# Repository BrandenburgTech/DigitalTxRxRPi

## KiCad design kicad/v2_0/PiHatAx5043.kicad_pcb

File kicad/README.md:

v1_3 - Digital Transceiver for the Raspberry Pi with the AX5043

v1_3_5 - Digital Transceiver for the Raspberry Pi with the AX5243

v2_0 - Digital Transceiver for the Raspberry Pi with the AX5043, power amplifier, and GPS module

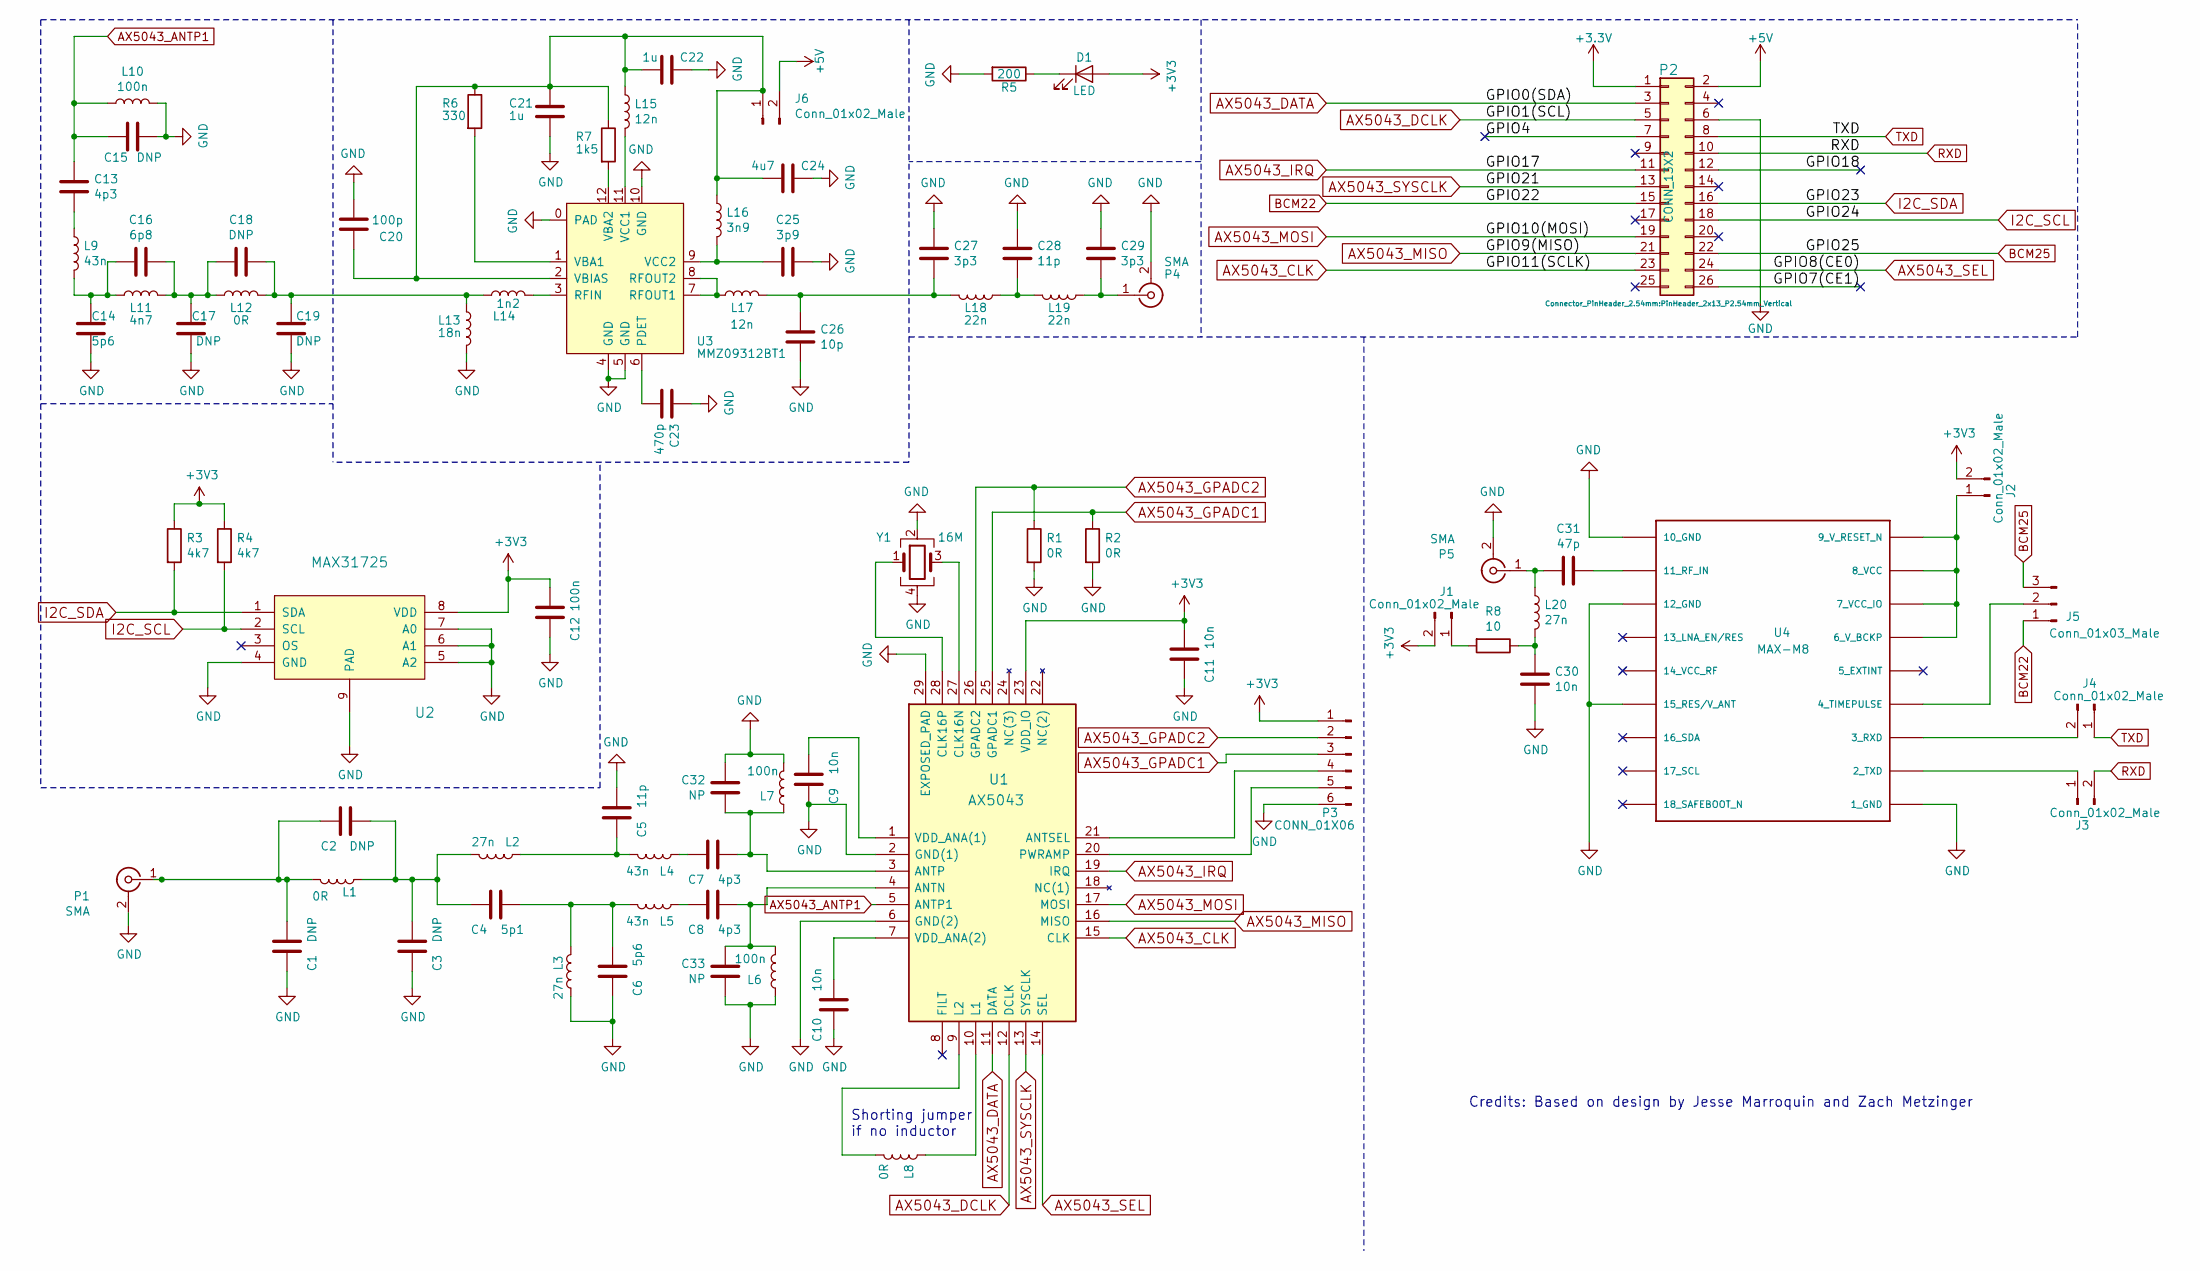
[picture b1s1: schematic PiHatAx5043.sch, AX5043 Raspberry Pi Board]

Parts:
C1, C2, C3, C15, C17, C18, C19: DNP; C_0603_1608Metric
C4: 5p1; C_0603_1608Metric
C5, C28: 11p; C_0603_1608Metric
C6, C14: 5p6; C_0603_1608Metric
C7, C8, C13: 4p3; C_0603_1608Metric
C9, C10, C11, C30: 10n; C_0603_1608Metric
C12: 100n; C_0603_1608Metric
C16: 6p8; C_0603_1608Metric
C20: 100p; C_0603_1608Metric
C21, C22: 1u; C_0603_1608Metric
C23: 470p; C_0603_1608Metric
C24: 4u7; C_0603_1608Metric
C25: 3p9; C_0603_1608Metric
C26: 10p; C_0603_1608Metric
C27, C29: 3p3; C_0603_1608Metric
C31: 47p; C_0603_1608Metric
C32, C33: NP; C_0603_1608Metric
D1: LED; LED_0603_1608Metric
J1, J2, J3, J4, J6: Conn_01x02_Male; PinHeader_1x02_P2.54mm_Vertical
J5: Conn_01x03_Male; PinHeader_1x03_P2.54mm_Vertical
L1, L8, L12: 0R; L_0603_1608Metric
L2, L3, L20: 27n; L_0603_1608Metric
L4, L5, L9: 43n; L_0603_1608Metric
L6, L7, L10: 100n; L_0603_1608Metric
L11: 4n7; L_0603_1608Metric
L13: 18n; L_0603_1608Metric
L14: 1n2; L_0603_1608Metric
L15, L17: 12n; L_0603_1608Metric
L16: 3n9; L_0603_1608Metric
L18, L19: 22n; L_0603_1608Metric
P1, P4, P5: SMA; SMA_Amphenol_901-144_Vertical
P2: CONN_13X2; PinHeader_2x13_P2.54mm_Vertical
P3: CONN_01X06; PinHeader_1x06_P2.54mm_Vertical
R1, R2: 0R; R_0603_1608Metric
R3, R4: 4k7; R_0603_1608Metric
R5: 200; R_0603_1608Metric
R6: 330; R_0603_1608Metric
R7: 1k5; R_0603_1608Metric
R8: 10; R_0603_1608Metric
U1: AX5043; QFN50P500X500X95-29N
U2: MAX31725; DFN-8-1EP_3x3mm_P0.65mm_EP1.55x2.4mm
U3: MMZ09312BT1; QFN-12-1EP_3x3mm_P0.5mm_EP1.65x1.65mm_ThermalVias
U4: MAX-M8
Y1: 16M; Crystal_SMD_ECX42-4pin_4.0x2.5mm

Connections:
+5V: J6.2, P2.2
/GPIO4: P2.7
/GPIO7(CE1): P2.26
/GPIO18: P2.12
AX5043_ANTP1: C13.1, C15.2, L10.1, U1.5 (ANTP1)
AX5043_CLK: P2.23, U1.15 (CLK)
AX5043_DATA: P2.3, U1.11 (DATA)
AX5043_DCLK: P2.5, U1.12 (DCLK)
AX5043_GPADC1: P3.3, R2.1, U1.25 (GPADC1)
AX5043_GPADC2: P3.2, R1.1, U1.26 (GPADC2)
AX5043_IRQ: P2.11, U1.19 (IRQ)
AX5043_MISO: P2.21, U1.16 (MISO)
AX5043_MOSI: P2.19, U1.17 (MOSI)
AX5043_SEL: P2.24, U1.14 (SEL)
AX5043_SYSCLK: P2.13, U1.13 (SYSCLK)
BCM22: J5.1, P2.15
BCM25: J5.3, P2.22
GND: C1.2, C3.2, C5.1, C6.2, C9.2, C10.2, C11.2, C12.2, C14.2, C15.1, C17.2, C19.2, C20.2, C21.2, C22.1, C23.1, C24.1, C25.1, C26.2, C27.1, C28.1, C29.1, C30.2, C32.2, C33.1, L3.1, L6.1, L7.2, L10.2, L13.2, P1.2 (Ext), P2.6, P3.6, P4.2 (Ext), P5.2 (Ext), R1.2, R2.2, R5.2, U1.2 (GND(1)), U1.6 (GND(2)), U1.29 (EXPOSED_PAD), U2.4 (GND), U2.5 (A2), U2.6 (A1), U2.7 (A0), U2.9 (PAD), U3.0 (PAD), U3.4 (GND), U3.5 (GND), U3.10 (GND), U3.13, U4.1_GND, U4.10_GND, U4.12_GND, U4.15_V_ANT/RESERVED (15_RES/V_ANT), Y1.2, Y1.4
I2C_SCL: P2.18, R4.2, U2.2 (SCL)
I2C_SDA: P2.16, R3.2, U2.1 (SDA)
unnamed: C1.1, C2.2, L1.2, P1.1 (In)
unnamed: C2.1, C3.1, C4.2, L1.1, L2.2
unnamed: C4.1, C6.1, L3.2, L5.2
unnamed: C5.2, L2.1, L4.2
unnamed: C7.2, L4.1
unnamed: C8.2, L5.1
unnamed: C9.1, U1.1 (VDD_ANA(1))
unnamed: C10.1, U1.7 (VDD_ANA(2))
unnamed: C13.2, L9.1
unnamed: C14.1, C16.2, L9.2, L11.1
unnamed: C16.1, C17.1, C18.2, L11.2, L12.1
unnamed: C18.1, C19.1, L12.2, L13.1, L14.1
unnamed: C20.1, C21.1, C22.2, C24.2, J6.1, L15.1, L16.1, R6.1, R7.1, U3.2 (VBIAS)
unnamed: C23.2, U3.6 (PDET)
unnamed: C25.2, L16.2, U3.9 (VCC2)
unnamed: C26.1, C27.2, L17.2, L18.2
unnamed: C28.2, L18.1, L19.2
unnamed: C29.2, L19.1, P4.1 (In)
unnamed: C30.1, L20.2, R8.1
unnamed: C31.1, U4.11_RF_IN
unnamed: C31.2, L20.1, P5.1 (In)
unnamed: C7.1, C32.1, L7.1, U1.3 (ANTP)
unnamed: C8.1, C33.2, L6.2, U1.4 (ANTN)
unnamed: D1.1 (K), R5.1
unnamed: J1.1, R8.2
unnamed: J2.1, U4.6_V_BCKP, U4.7_VCC_IO, U4.8_VCC, U4.9_RESET_N (9_V_RESET_N)
unnamed: J3.1, U4.2_TXD
unnamed: J4.2, U4.3_RXD
unnamed: J5.2, U4.4_TIMEPULSE
unnamed: L8.1, U1.10 (L1)
unnamed: L8.2, U1.9 (L2)
unnamed: L14.2, U3.3 (RFIN)
unnamed: L15.2, U3.11 (VCC1)
unnamed: L17.1, U3.7 (RFOUT1), U3.8 (RFOUT2)
unnamed: P3.4, U1.21 (ANTSEL)
unnamed: P3.5, U1.20 (PWRAMP)
unnamed: R6.2, U3.1 (VBA1)
unnamed: R7.2, U3.12 (VBA2)
unnamed: U1.27 (CLK16N), Y1.3
unnamed: U1.28 (CLK16P), Y1.1
RXD: J3.2, P2.10
TXD: J4.1, P2.8

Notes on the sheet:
Shorting jumper if no inductor
Credits: Based on design by Jesse Marroquin and Zach Metzinger

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
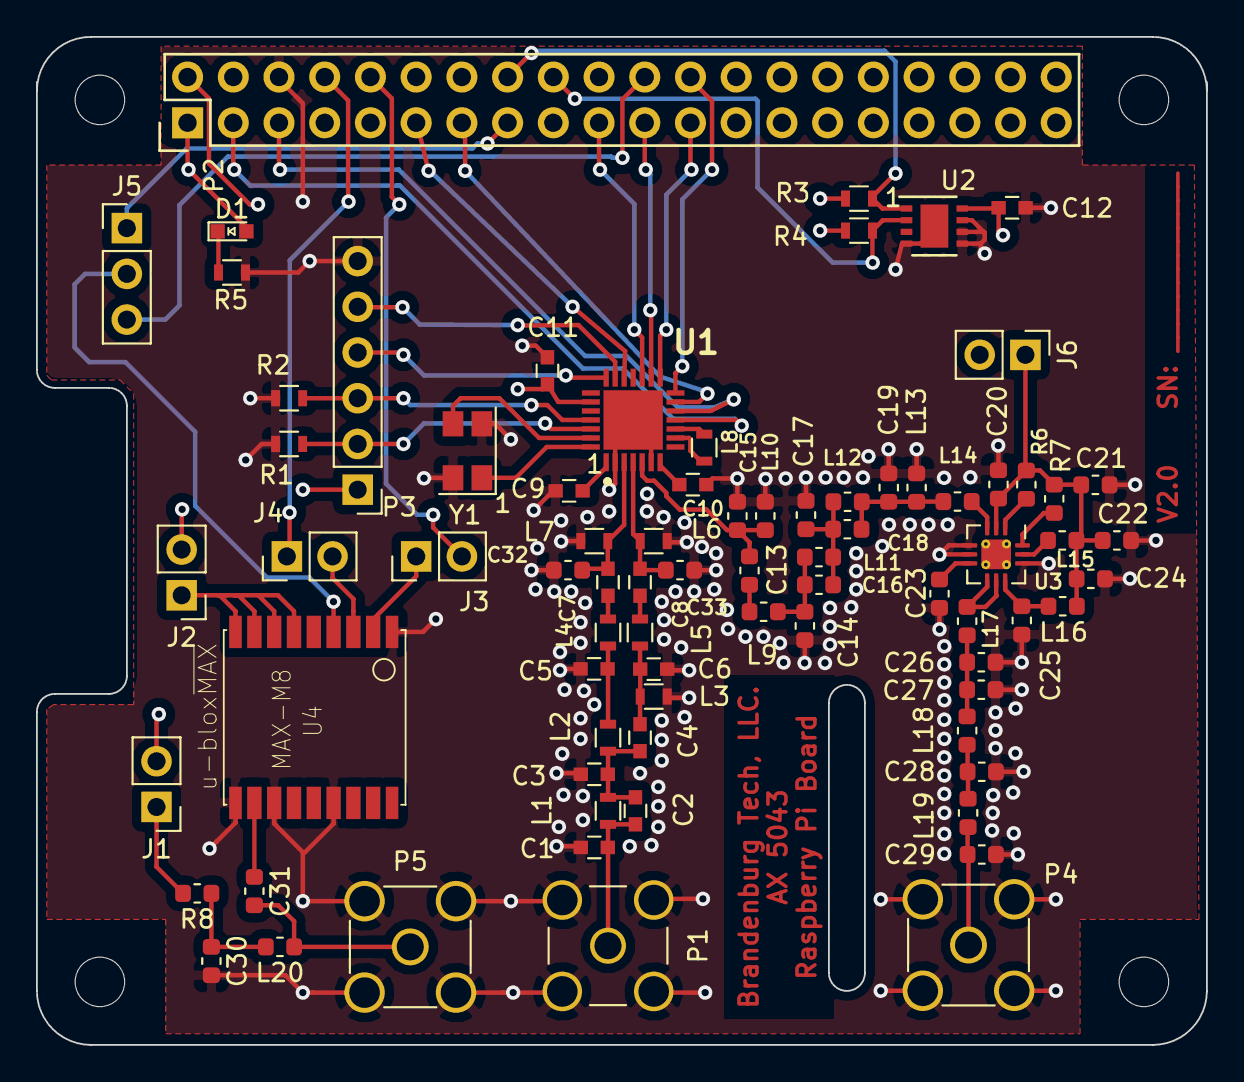
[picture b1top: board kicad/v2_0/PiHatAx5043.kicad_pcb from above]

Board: 4 copper layers, 65.0 x 56.0 mm, 78 parts (0 on the bottom side), 60 nets.

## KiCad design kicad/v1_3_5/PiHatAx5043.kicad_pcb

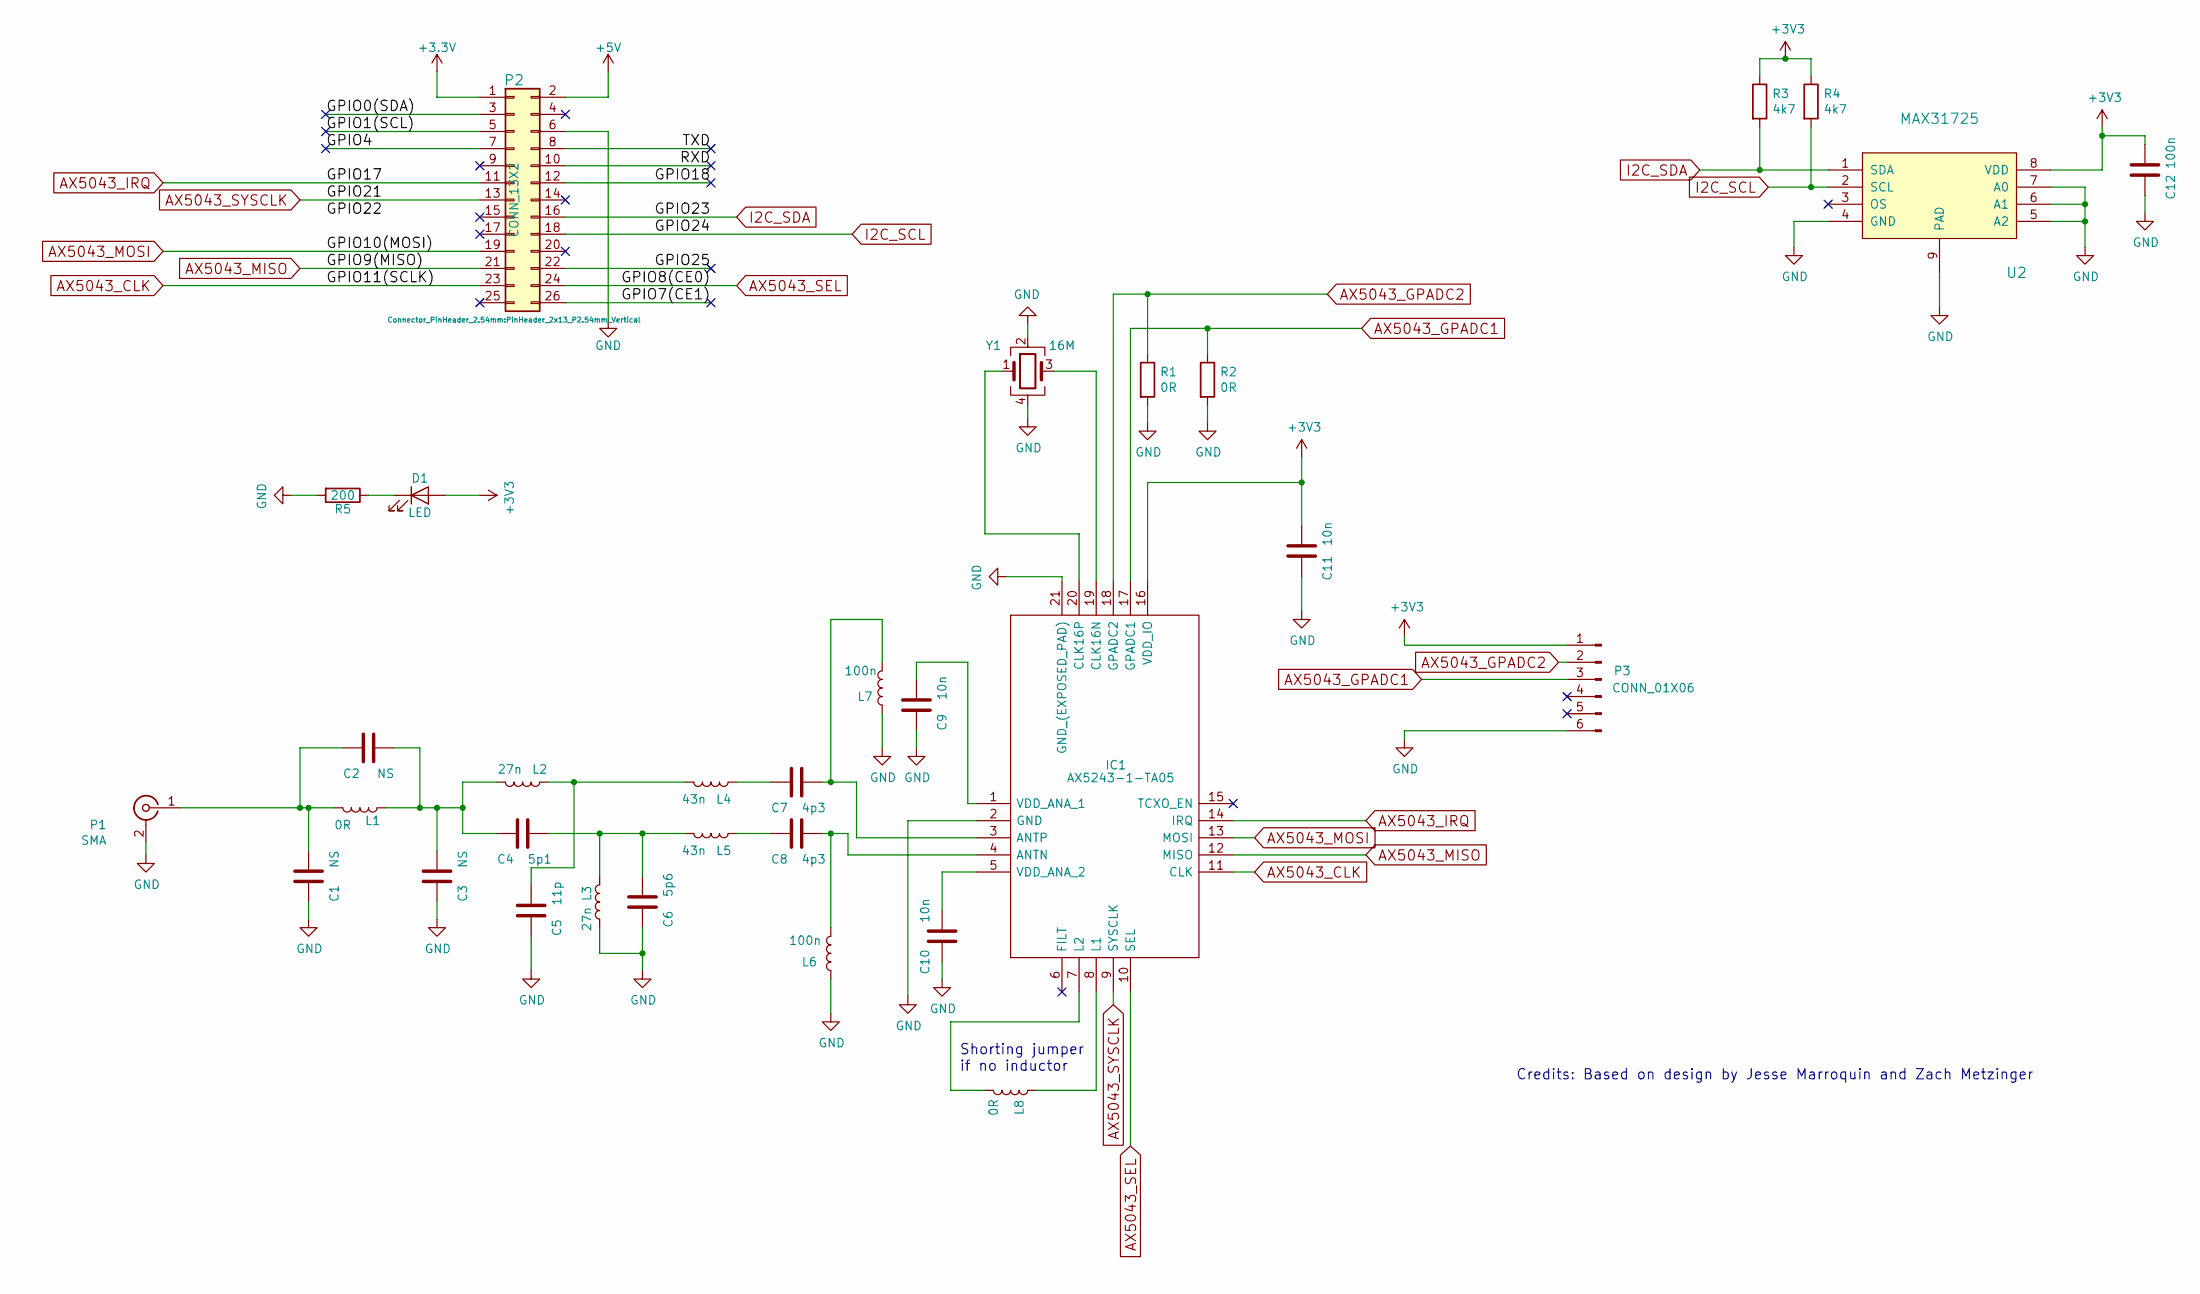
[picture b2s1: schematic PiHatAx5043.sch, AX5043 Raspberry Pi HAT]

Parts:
C1, C2, C3: NS; C_0603_1608Metric
C4: 5p1; C_0603_1608Metric
C5: 11p; C_0603_1608Metric
C6: 5p6; C_0603_1608Metric
C7, C8: 4p3; C_0603_1608Metric
C9, C10, C11: 10n; C_0603_1608Metric
C12: 100n; C_0603_1608Metric
D1: LED; LED_0603_1608Metric
IC1: AX5243-1-TA05; QFN50P400X400X100-21N; Manufacturer_Part_Number AX5243-1-TA05; Mouser Part Number 863-AX5243-1-TA05
L1, L8: 0R; L_0603_1608Metric
L2, L3: 27n; L_0603_1608Metric
L4, L5: 43n; L_0603_1608Metric
L6, L7: 100n; L_0603_1608Metric
P1: SMA; SMA_Amphenol_901-144_Vertical
P2: CONN_13X2; PinHeader_2x13_P2.54mm_Vertical
P3: CONN_01X06; PinHeader_1x06_P2.54mm_Vertical
R1, R2: 0R; R_0603_1608Metric
R3, R4: 4k7; R_0603_1608Metric
R5: 200; R_0603_1608Metric
U2: MAX31725; DFN-8-1EP_3x3mm_P0.65mm_EP1.55x2.4mm
Y1: 16M; Crystal_SMD_ECX42-4pin_4.0x2.5mm

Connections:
+5V: P2.2
/GPIO0(SDA): P2.3
/GPIO1(SCL): P2.5
/GPIO4: P2.7
/GPIO7(CE1): P2.26
/GPIO18: P2.12
/GPIO25: P2.22
/RXD: P2.10
/TXD: P2.8
AX5043_CLK: IC1.11 (CLK), P2.23
AX5043_GPADC1: IC1.17 (GPADC1), P3.3, R2.1
AX5043_GPADC2: IC1.18 (GPADC2), P3.2, R1.1
AX5043_IRQ: IC1.14 (IRQ), P2.11
AX5043_MISO: IC1.12 (MISO), P2.21
AX5043_MOSI: IC1.13 (MOSI), P2.19
AX5043_SEL: IC1.10 (SEL), P2.24
AX5043_SYSCLK: IC1.9 (SYSCLK), P2.13
GND: C1.2, C3.2, C5.2, C6.2, C9.2, C10.2, C11.2, C12.2, IC1.2 (GND), IC1.21 (GND_(EXPOSED_PAD)), L3.1, L6.1, L7.1, P1.2 (Ext), P2.6, P3.6, R1.2, R2.2, R5.2, U2.4 (GND), U2.5 (A2), U2.6 (A1), U2.7 (A0), U2.9 (PAD), Y1.2, Y1.4
I2C_SCL: P2.18, R4.2, U2.2 (SCL)
I2C_SDA: P2.16, R3.2, U2.1 (SDA)
unnamed: C1.1, C2.2, L1.2, P1.1 (In)
unnamed: C2.1, C3.1, C4.2, L1.1, L2.2
unnamed: C4.1, C6.1, L3.2, L5.2
unnamed: C5.1, L2.1, L4.2
unnamed: C7.1, IC1.3 (ANTP), L7.2
unnamed: C7.2, L4.1
unnamed: C8.1, IC1.4 (ANTN), L6.2
unnamed: C8.2, L5.1
unnamed: C9.1, IC1.1 (VDD_ANA_1)
unnamed: C10.1, IC1.5 (VDD_ANA_2)
unnamed: D1.1 (K), R5.1
unnamed: IC1.7 (L2), L8.2
unnamed: IC1.8 (L1), L8.1
unnamed: IC1.19 (CLK16N), Y1.3
unnamed: IC1.20 (CLK16P), Y1.1

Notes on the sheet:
Shorting jumper if no inductor
Credits: Based on design by Jesse Marroquin and Zach Metzinger

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
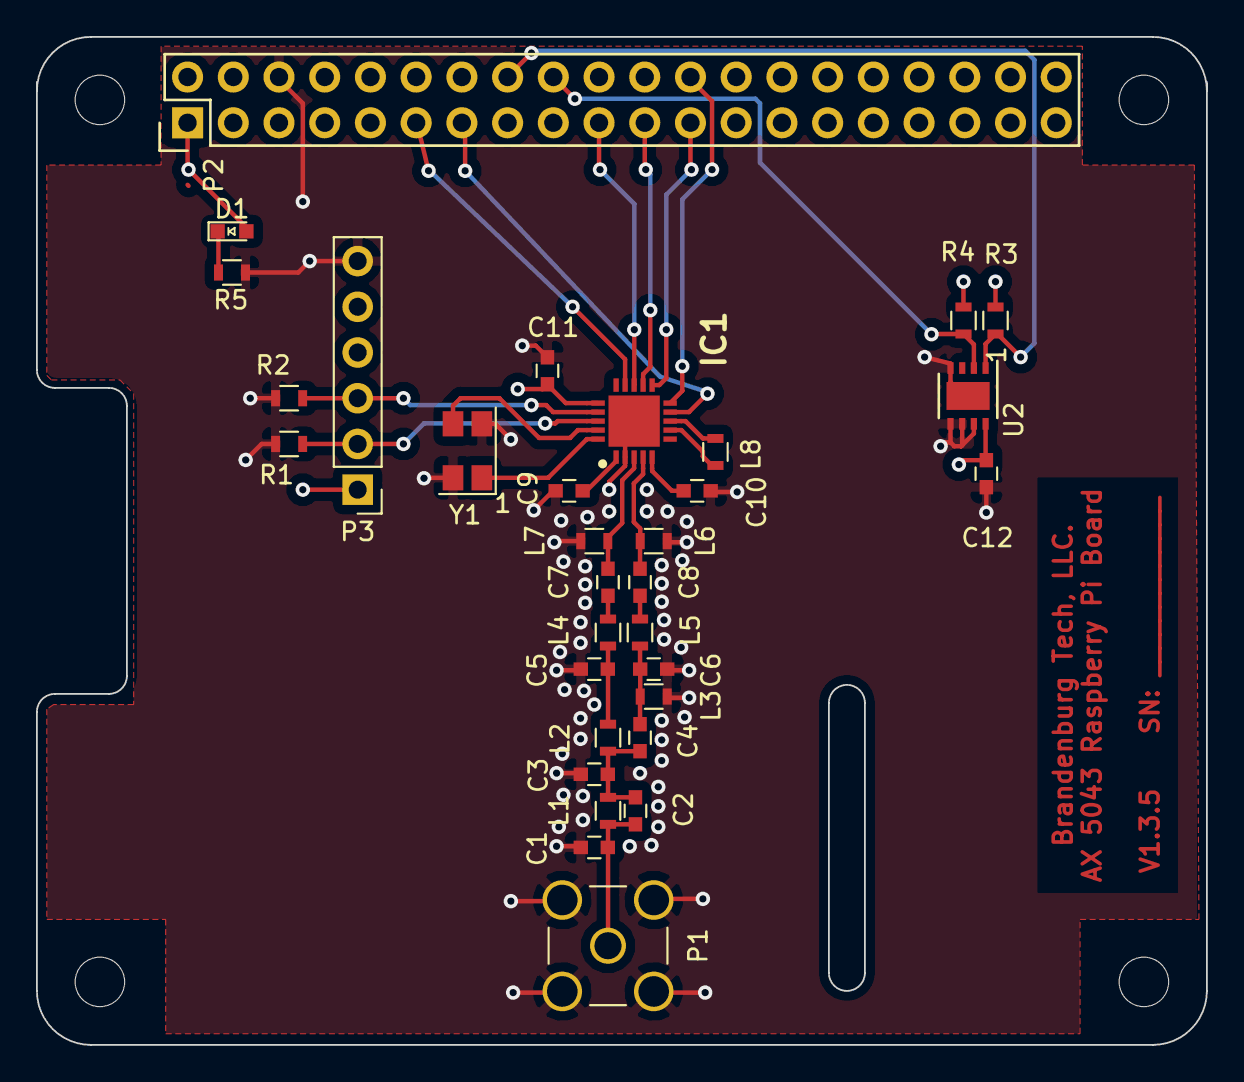
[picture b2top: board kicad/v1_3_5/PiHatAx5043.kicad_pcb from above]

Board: 4 copper layers, 65.0 x 56.0 mm, 32 parts (0 on the bottom side), 27 nets.

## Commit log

2018-10-17 Updated license headers
2018-11-03 Fix the AX.25 PID (from 0x0f to 0xf0)
2019-07-11 Fixing a bug in the autoranging code. Thanks to Alan Johnston for identifying the issue and suggesting a solution.
2022-10-25 Add prototype 1.3.5 and 1.4 kicad files. These have not been assembled or tested
